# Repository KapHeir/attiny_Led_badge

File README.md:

# ATtiny LED Badge

A decorative LED badge project based on the ATtiny85 microcontroller.  
This repository contains a star-shaped PCB version and a future heart-shaped PCB version.

The current completed version is the **star-shaped badge**, which uses 5 LEDs, a push button, a CR2032 battery holder, and an ATtiny85 to generate multiple LED animation patterns.

---

# Project Overview

This project was created as a decorative and educational PCB badge design using KiCad and an ATtiny85 microcontroller.

The badge is designed to:
- blink and animate multiple LEDs
- switch between animation modes using a push button
- run from a small battery
- demonstrate both PCB design and embedded control with a microcontroller

This repository is also intended as a portfolio-style project that shows:
- schematic design
- PCB layout
- Gerber generation
- GitHub project organization
- basic embedded programming with ATtiny85

---

# Features

- ATtiny85-based LED control
- 5 LED outputs
- Push button input
- On/off switch
- CR2032 battery powered
- Compact decorative PCB concept
- Designed in KiCad
- Example code included
- Expandable to multiple visual themes

---

# Repository Structure

```text
attiny-led-badge/
│
├── README.md
│
├── star_shape/
│   ├── kicad/
│   ├── gerbers/
│   ├── images/
│   └── code/
│
└── heart_shape/
    ├── kicad/
    ├── gerbers/
    ├── images/
    └── code/

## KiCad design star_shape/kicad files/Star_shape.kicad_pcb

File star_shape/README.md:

# Star Shape ATtiny85 LED Badge

A star-shaped LED badge built around the **ATtiny85** microcontroller.  
This project combines decorative PCB design, embedded programming, and compact battery-powered LED animation in a single board.

The badge is designed as both:
- a visual electronics project
- an educational ATtiny85 + KiCad portfolio project

---

## 1. Project Purpose

The goal of this project is to create a **star-shaped PCB badge** that can drive multiple LEDs with animation patterns using an **ATtiny85**.

This project is useful for learning:
- schematic design in KiCad
- PCB layout and routing
- generating Gerber and drill files
- using an ATtiny85 in a real hardware design
- programming through a 2x3 AVR ISP header
- designing decorative shape-based PCBs

---

## 2. Main Features

- Star-shaped PCB
- ATtiny85 microcontroller
- 5 LEDs
- Push button for interaction / mode changing
- On/off switch
- CR2032 battery powered
- ISP programming header
- Compact embedded design
- Suitable for decorative and educational use

---

## 3. What This Badge Can Do

This badge can be programmed to run different LED animations such as:
- sequential LED blinking
- alternating patterns
- all LEDs flashing together
- rotating or circular patterns
- mirrored animations
- idle and active modes
- button-controlled animation mode switching

With firmware changes, the project can be expanded further.

---

## 4. Folder Structure

```text
star_shape/
├── kicad/
│   ├── star_shape.kicad_pro
│   ├── star_shape.kicad_sch
│   └── star_shape.kicad_pcb
│
├── gerbers/
│   ├── ...fabrication files...
│
├── images/
│   ├── pcb.png
│   ├── schematic.png
│   ├── 3d view.png
│   ├── bom-table.png
│   └── Header.png
│
└── code/
    └── attiny_led_demo.ino
```

## 5. Hardware Overview

The badge is built around the **ATtiny85**, which controls the LEDs and reads the push button.

### Main hardware blocks

- ATtiny85: main controller
- 5 LEDs: visual output
- 5 current-limiting resistors
- Push button: user input
- On/off switch: power control
- CR2032 battery holder: portable power source
- 100nF capacitor: supply decoupling
- 10k resistor: reset pull-up
- 2x3 ISP header: programming interface

---

## 6. Bill of Materials (BOM)

A BOM image is included here:

Typical component list:
- 1 × ATtiny85
- 5 × LEDs
- 5 × 220Ω resistors
- 1 × 10kΩ resistor
- 1 × 100nF capacitor
- 1 × push button
- 1 × on/off switch
- 1 × CR2032 battery holder
- 1 × 2x3 ISP header

---

## 7. PCB Images

### PCB Layout

### Schematic

### 3D View

---

## 8. Pin Mapping

The ATtiny85 pins are used for LED control, button input, reset handling, and programming.

### Functional mapping

- **PB0** → LED control / programming line
- **PB1** → LED control / programming line
- **PB2** → LED control / programming line
- **PB4** → push button input
- **PB5 / RESET** → reset line
- **VCC / GND** → power input

Because this is a compact design, some pins are shared carefully between LED control and programming functions.

---

## 9. ISP Header Connections

The board uses a standard **2x3 AVR ISP header** for programming the ATtiny85.

### ISP header mapping

- **Pin 1** → RESET
- **Pin 2** → VCC
- **Pin 3** → PB1 / MOSI
- **Pin 4** → PB0 / MISO
- **Pin 5** → PB2 / SCK
- **Pin 6** → GND

A visual reference is included here:

---

## 10. How to Power the Board

This project is designed to run from a **CR2032 coin cell battery**.

### Power path

1. Insert the CR2032 battery into the holder.
2. Turn the board on using the on/off switch.
3. The ATtiny85 receives power and starts running the programmed animation.

### Notes

- The CR2032 is compact and suitable for lightweight badge-style projects.
- LED brightness and current usage should be considered to avoid draining the battery too quickly.
- The firmware can be optimized later for lower power consumption.

---

## 11. How to Program the ATtiny85

The ATtiny85 on this board is programmed through the **2x3 AVR ISP header**.

This project can be programmed using:
- **Arduino as ISP**
- **USBasp**
- other AVR-compatible programmers

The most beginner-friendly method is usually **Arduino as ISP**.

---

### 11.1 Programming Method Used in This Project

In this project, the ATtiny85 can be programmed using an **Arduino board as an ISP programmer**.

A common setup is:
- Arduino Uno
- jumper wires
- the 2x3 ISP header on the badge PCB

---

### 11.2 ISP Header Pin Functions

The 2x3 programming header on the PCB is connected like this:

- **Pin 1** → RESET
- **Pin 2** → VCC
- **Pin 3** → PB1 / MOSI
- **Pin 4** → PB0 / MISO
- **Pin 5** → PB2 / SCK
- **Pin 6** → GND

These are the programming-related lines used by the ATtiny85.

---

### 11.3 Arduino as ISP Connections

If you use an **Arduino Uno as ISP**, connect it to the badge as follows:

- **Arduino D10** → **RESET** (ISP header Pin 1)
- **Arduino 5V** → **VCC** (ISP header Pin 2)
- **Arduino D11** → **MOSI / PB1** (ISP header Pin 3)
- **Arduino D12** → **MISO / PB0** (ISP header Pin 4)
- **Arduino D13** → **SCK / PB2** (ISP header Pin 5)
- **Arduino GND** → **GND** (ISP header Pin 6)
---

## 12. Example Firmware

An example firmware file is included in:

```text
code/attiny_led_demo.ino
```

This demo code shows how to:
- initialize the LED pins
- read the push button
- switch animation modes
- generate several LED patterns

### Example behavior
- mode 1: sequential blink
- mode 2: alternating blink
- mode 3: all LEDs flash
- mode 4: rotating pattern

---

## 13. How the Example Code Works

The example firmware performs these steps:

### Startup
- initialize LED pins as outputs
- configure the button pin as input with pull-up
- set the default animation mode

### Main loop
- check the push button
- change mode when the button is pressed
- run the selected animation

### Animation logic
The firmware cycles through multiple visual modes:
- sequential blinking
- alternating groups
- all LEDs flashing together
- rotating movement effect

This demonstrates:
- digital output control
- button reading
- mode switching
- timing-based animation logic

---

## 14. How to Use the Badge

### Basic use
1. Insert the battery.
2. Turn on the power switch.
3. Observe the default animation.
4. Press the button to change animation modes.

### Educational use
This board can be used to practice:
- ATtiny programming
- LED control logic
- low-power design basics
- decorative PCB design

### Demonstration use
This board can also be used as:
- a portfolio project
- a classroom demonstration
- a beginner embedded systems example
- a decorative wearable electronics concept

---

## 15. What You Can Modify

This project is intentionally flexible.

You can improve or customize it by changing:
- LED colors
- animation timing
- button behavior
- board artwork
- number of modes
- power optimization strategy
- LED placement for a different star style

You can also reuse the same design idea for:
- a heart-shaped badge
- a logo-shaped PCB
- a gift badge
- a themed wearable board

---

## 16. Design Notes

This project was built as a practical exercise in:
- KiCad schematic capture
- PCB layout and routing
- Gerber generation
- ATtiny85 hardware integration
- GitHub documentation and project organization

It is not just a blinking LED board; it is intended as a compact, polished, and shareable design project.

---

## 17. Manufacturing Notes

Fabrication files are stored in:

```text
star_shape/Gerber and drill files
```

These include:
- copper layers
- mask layers
- silkscreen layers
- board outline
- drill files

Before fabrication, always verify:
- LED polarity
- ATtiny85 orientation
- switch footprint compatibility
- battery holder footprint compatibility
- programming header orientation

---

## 18. Recommended Checks Before Assembly

Before ordering or soldering the board, check:
- ATtiny85 pin orientation
- LED polarity
- resistor values
- push button footprint
- on/off switch footprint
- battery holder footprint
- ISP header orientation
- solder bridge risk on small pads
- board outline integrity

---

## 19. Suggested Improvements for Future Revisions

Possible future improvements:
- lower power firmware
- PWM fade animations
- cleaner visual LED symmetry
- fully optimized badge layout
- assembly photographs
- finished hardware photos
- animated GIF or demo video
- alternate shape variants

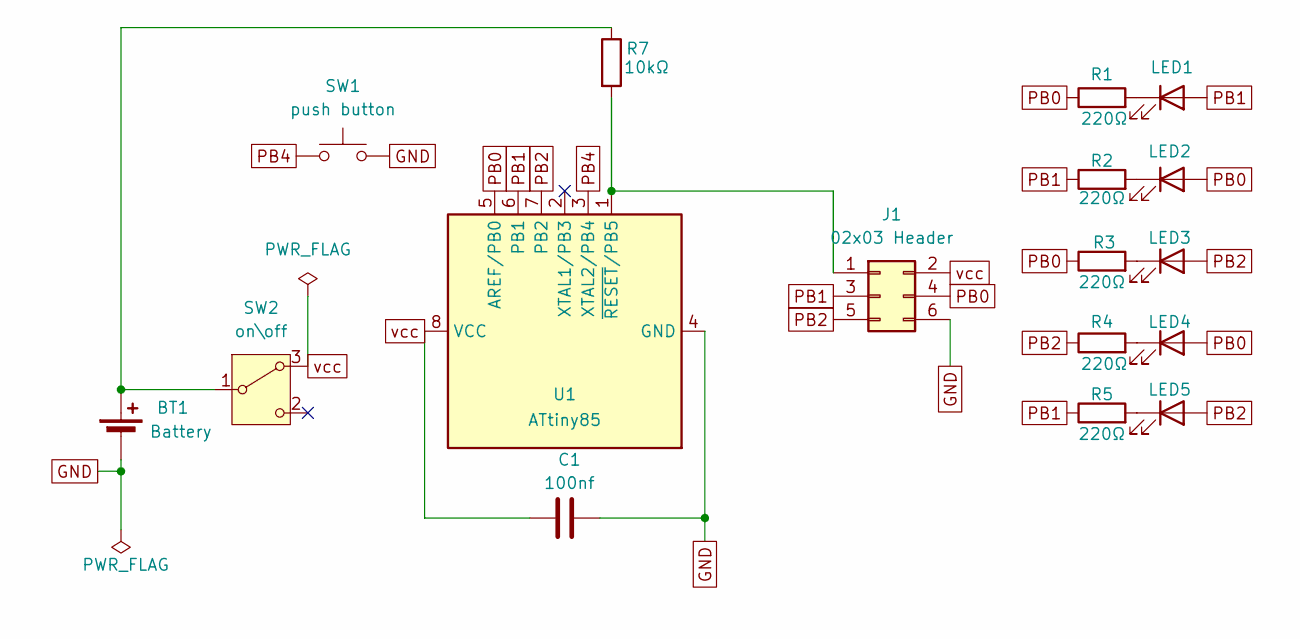
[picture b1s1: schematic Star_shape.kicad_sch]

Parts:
BT1: Battery; BatteryHolder_Keystone_3034_1x20mm
C1: 100nf; C_1206_3216Metric
D1: LED1; LED_1206_3216Metric
D2: LED2; LED_1206_3216Metric
D3: LED3; LED_1206_3216Metric
D4: LED4; LED_1206_3216Metric
D5: LED5; LED_1206_3216Metric
J1: 02x03 Header; PinHeader_2x03_P2.54mm_Vertical
R1, R2, R3, R4, R5: 220Ω; R_1206_3216Metric
R7: 10kΩ; R_1206_3216Metric
SW1: push button; SW_PUSH_1P1T_6x3.5mm_H4.3_APEM_MJTP1243
SW2: on\off; SW_Slide-03_Wuerth-WS-SLTV_10x2.5x6.4_P2.54mm
U1: ATtiny85; SOIC-8_5.3x5.3mm_P1.27mm

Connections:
GND: BT1.2 (-), C1.2, J1.6, SW1.2, U1.4 (GND)
unnamed: BT1.1 (+), R7.1, SW2.1 (B)
unnamed: D1.1 (K), R1.2
unnamed: D2.1 (K), R2.2
unnamed: D3.1 (K), R3.2
unnamed: D4.1 (K), R4.2
unnamed: D5.1 (K), R5.2
unnamed: J1.1, R7.2, U1.1 (~RESET/PB5)
PB0: D2.2 (A), D4.2 (A), J1.4, R1.1, R3.1, U1.5 (AREF/PB0)
PB1: D1.2 (A), J1.3, R2.1, R5.1, U1.6 (PB1)
PB2: D3.2 (A), D5.2 (A), J1.5, R4.1, U1.7 (PB2)
PB4: SW1.1, U1.3 (XTAL2/PB4)
vcc: C1.1, J1.2, SW2.3 (A), U1.8 (VCC)

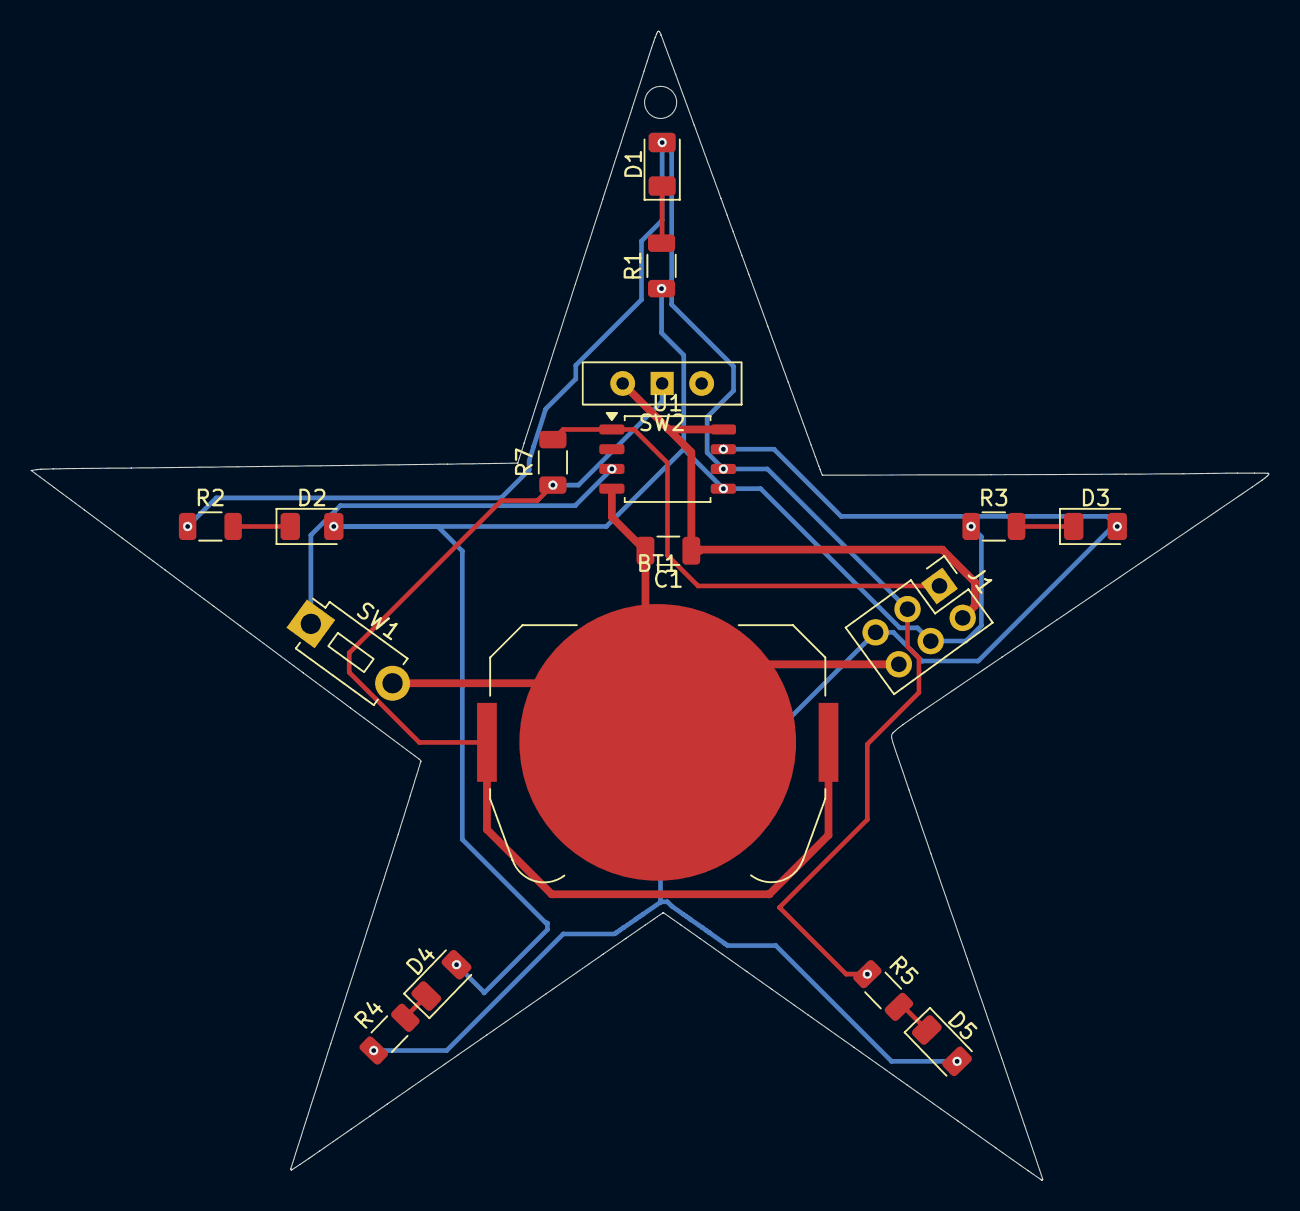
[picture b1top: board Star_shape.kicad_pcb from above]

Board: 2 copper layers, 79.6 x 73.9 mm, 17 parts (0 on the bottom side), 13 nets.

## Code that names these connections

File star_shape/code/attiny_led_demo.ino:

/*
  Star Shape ATtiny85 LED Badge Demo - 5 LED Version

  This example uses 5 LEDs with charlieplexing on:
  - PB0
  - PB1
  - PB2

  Push button:
  - PB4

  LED mapping assumed in this example:
  - LED1: PB0 -> PB1
  - LED2: PB1 -> PB0
  - LED3: PB0 -> PB2
  - LED4: PB2 -> PB0
  - LED5: PB1 -> PB2
*/

const int buttonPin = 4;   // PB4

const int pinA = 0;        // PB0
const int pinB = 1;        // PB1
const int pinC = 2;        // PB2

int mode = 0;
bool lastButtonState = HIGH;
unsigned long lastDebounceTime = 0;
const unsigned long debounceDelay = 50;

// --- Helper functions ---

void allPinsHiZ() {
  pinMode(pinA, INPUT);
  pinMode(pinB, INPUT);
  pinMode(pinC, INPUT);

  digitalWrite(pinA, LOW);
  digitalWrite(pinB, LOW);
  digitalWrite(pinC, LOW);
}

void driveLed(int anodePin, int cathodePin) {
  allPinsHiZ();

  pinMode(anodePin, OUTPUT);
  pinMode(cathodePin, OUTPUT);

  digitalWrite(anodePin, HIGH);
  digitalWrite(cathodePin, LOW);
}

void ledOff() {
  allPinsHiZ();
}

// LED map
void lightLED1() { driveLed(pinA, pinB); } // PB0 -> PB1
void lightLED2() { driveLed(pinB, pinA); } // PB1 -> PB0
void lightLED3() { driveLed(pinA, pinC); } // PB0 -> PB2
void lightLED4() { driveLed(pinC, pinA); } // PB2 -> PB0
void lightLED5() { driveLed(pinB, pinC); } // PB1 -> PB2

void showLed(int ledNumber, int durationMs) {
  unsigned long startTime = millis();

  while (millis() - startTime < (unsigned long)durationMs) {
    switch (ledNumber) {
      case 1: lightLED1(); break;
      case 2: lightLED2(); break;
      case 3: lightLED3(); break;
      case 4: lightLED4(); break;
      case 5: lightLED5(); break;
      default: ledOff(); break;
    }
    delay(2);  // refresh for visible brightness
  }

  ledOff();
}

// --- Button handling ---

void handleButton() {
  bool reading = digitalRead(buttonPin);

  if (reading != lastButtonState) {
    lastDebounceTime = millis();
  }

  if ((millis() - lastDebounceTime) > debounceDelay) {
    if (reading == LOW && lastButtonState == HIGH) {
      mode++;
      if (mode > 3) {
        mode = 0;
      }
    }
  }

  lastButtonState = reading;
}

// --- Animation modes ---

void sequentialBlink() {
  showLed(1, 120);
  showLed(2, 120);
  showLed(3, 120);
  showLed(4, 120);
  showLed(5, 120);
}

void alternatingBlink() {
  // Group A
  showLed(1, 80);
  showLed(3, 80);
  showLed(5, 80);

  delay(80);

  // Group B
  showLed(2, 80);
  showLed(4, 80);

  delay(80);
}

void allFlash() {
  unsigned long startTime = millis();

  while (millis() - startTime < 250UL) {
    lightLED1(); delay(2);
    lightLED2(); delay(2);
    lightLED3(); delay(2);
    lightLED4(); delay(2);
    lightLED5(); delay(2);
  }

  ledOff();
  delay(180);
}

void rotatingPattern() {
  showLed(1, 70);
  showLed(2, 70);
  showLed(3, 70);
  showLed(4, 70);
  showLed(5, 70);
}

// --- Main program ---

void setup() {
  pinMode(buttonPin, INPUT_PULLUP);
  ledOff();
}

void loop() {
  handleButton();

  switch (mode) {
    case 0:
      sequentialBlink();
      break;
    case 1:
      alternatingBlink();
      break;
    case 2:
      allFlash();
      break;
    case 3:
      rotatingPattern();
      break;
    default:
      mode = 0;
      break;
  }
}

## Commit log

2026-03-20 Rename 3d View.png to 3d_View.png
2026-03-20 Rename value-name table.png to bom-table.png
